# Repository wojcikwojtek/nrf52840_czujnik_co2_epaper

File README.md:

# nrf52840_czujnik_co2_epaper
Projekt czujnika co2, temperatury i wilgotności zrobionym na procesorze nrf52840 z wykorzystaniem wyświetlacza typu epaper komunikującym się poprzez Matter

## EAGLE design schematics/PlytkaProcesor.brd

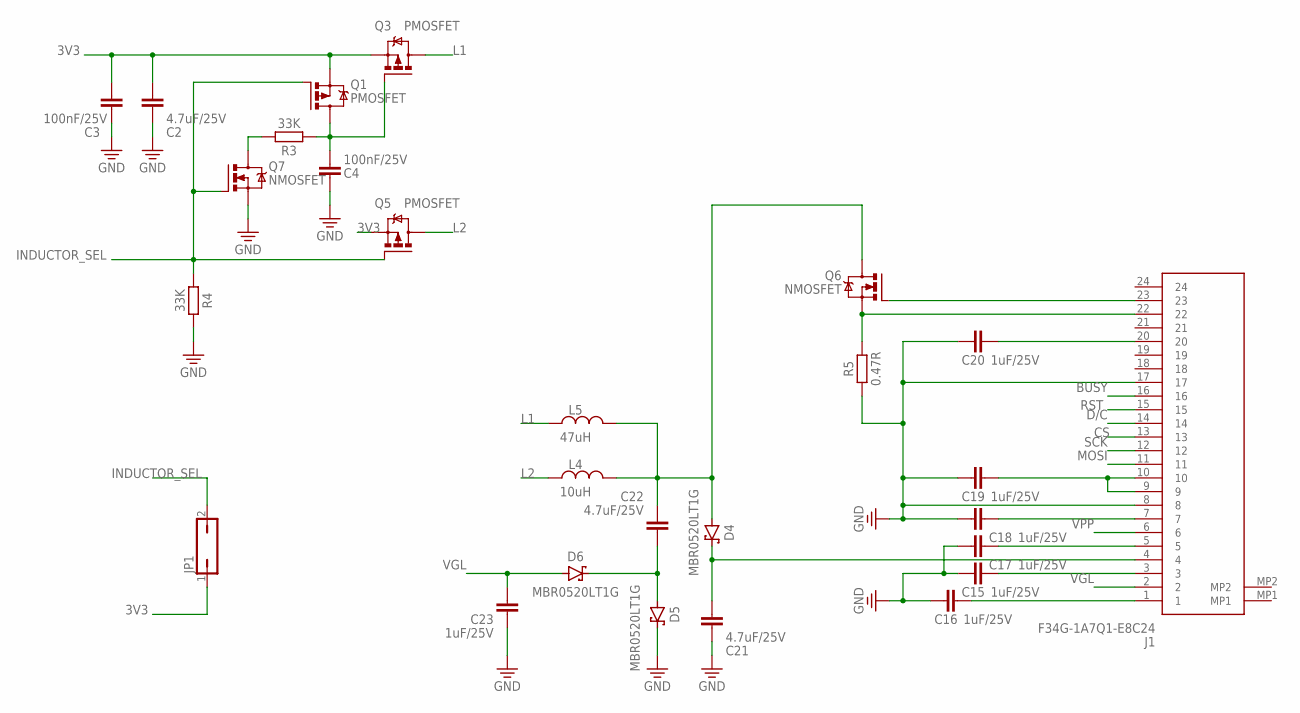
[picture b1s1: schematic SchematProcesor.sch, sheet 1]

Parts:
C2, C21, C22: 4.7uF/25V; CAPC1608X85
C3, C4: 100nF/25V; CAPC1608X85
C15, C16, C17, C18, C19, C20, C23: 1uF/25V; CAPC1608X85
D4, D5, D6: MBR0520LT1G; SODFL3718X115
J1: F34G-1A7Q1-E8C24; F34G1A7Q1E8C24
JP1: JP1Q; JP1
L4: 10uH; INDC1608X95N
L5: 47uH; INDC1608X95N
Q1, Q3, Q5: PMOSFET; SOT23
Q6, Q7: NMOSFET; SOT23
R3, R4: 33K; RESC1608X60
R5: 0.47R; RESC1608X60

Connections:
3V3: C2.2, C3.2, JP1.1, Q1.2 (S), Q3.2 (S), Q5.2 (S); also elsewhere on the board
BUSY: J1.16; also elsewhere on the board
CS: J1.13; also elsewhere on the board
D/C: J1.14; also elsewhere on the board
GND: C2.1, C3.1, C4.1, C15.1, C16.1, C17.1, C18.1, C19.1, C20.1, C21.1, C23.2, D5.1 (C), J1.8, J1.17, Q7.2 (S), R4.2, R5.1; also elsewhere on the board
INDUCTOR_SEL: JP1.2, Q1.1 (G), Q5.1 (G), Q7.1 (G), R4.1
L1: L5.1, Q3.3 (D)
L2: L4.1, Q5.3 (D)
MOSI: J1.11; also elsewhere on the board
unnamed: C4.2, Q1.3 (D), Q3.1 (G), R3.1
unnamed: C16.2, J1.1
unnamed: C15.2, J1.3
unnamed: C17.2, J1.5
unnamed: C18.2, J1.7
unnamed: C19.2, J1.9, J1.10
unnamed: Q7.3 (D), R3.2
unnamed: C20.2, J1.20
unnamed: J1.23, Q6.1 (G)
unnamed: J1.22, Q6.2 (S), R5.2
unnamed: C21.2, D4.1 (C), J1.4
unnamed: C22.1, D4.2 (A), L4.2, L5.2, Q6.3 (D)
unnamed: C22.2, D5.2 (A), D6.1 (C)
RST: J1.15; also elsewhere on the board
SCK: J1.12; also elsewhere on the board
VGL: C23.1, D6.2 (A), J1.2
VPP: J1.6

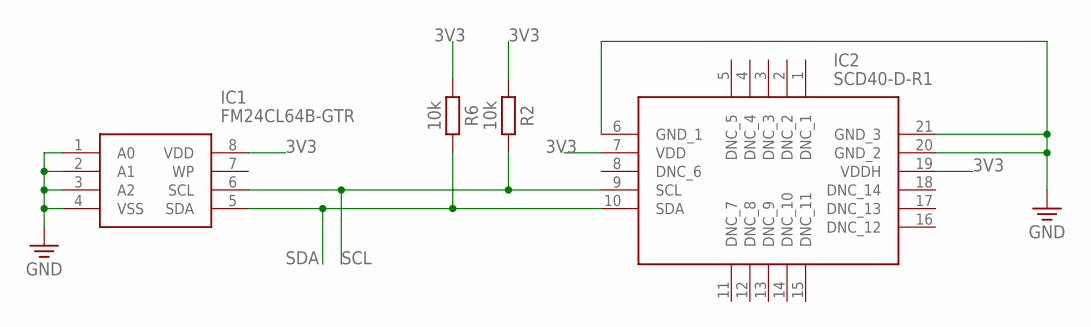
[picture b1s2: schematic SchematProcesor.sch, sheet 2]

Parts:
IC1: FM24CL64B-GTR; SOIC127P602X173-8N
IC2: SCD40-D-R1; SCD40DR1
R2, R6: 10k; RESC1608X60

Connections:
3V3: IC1.8 (VDD), IC2.7 (VDD), IC2.19 (VDDH), R2.1, R6.1; also elsewhere on the board
GND: IC1.1 (A0), IC1.2 (A1), IC1.3 (A2), IC1.4 (VSS), IC2.6 (GND_1), IC2.20 (GND_2), IC2.21 (GND_3); also elsewhere on the board
SCL: IC1.6 (SCL), IC2.9 (SCL), R2.2; also elsewhere on the board
SDA: IC1.5 (SDA), IC2.10 (SDA), R6.2; also elsewhere on the board

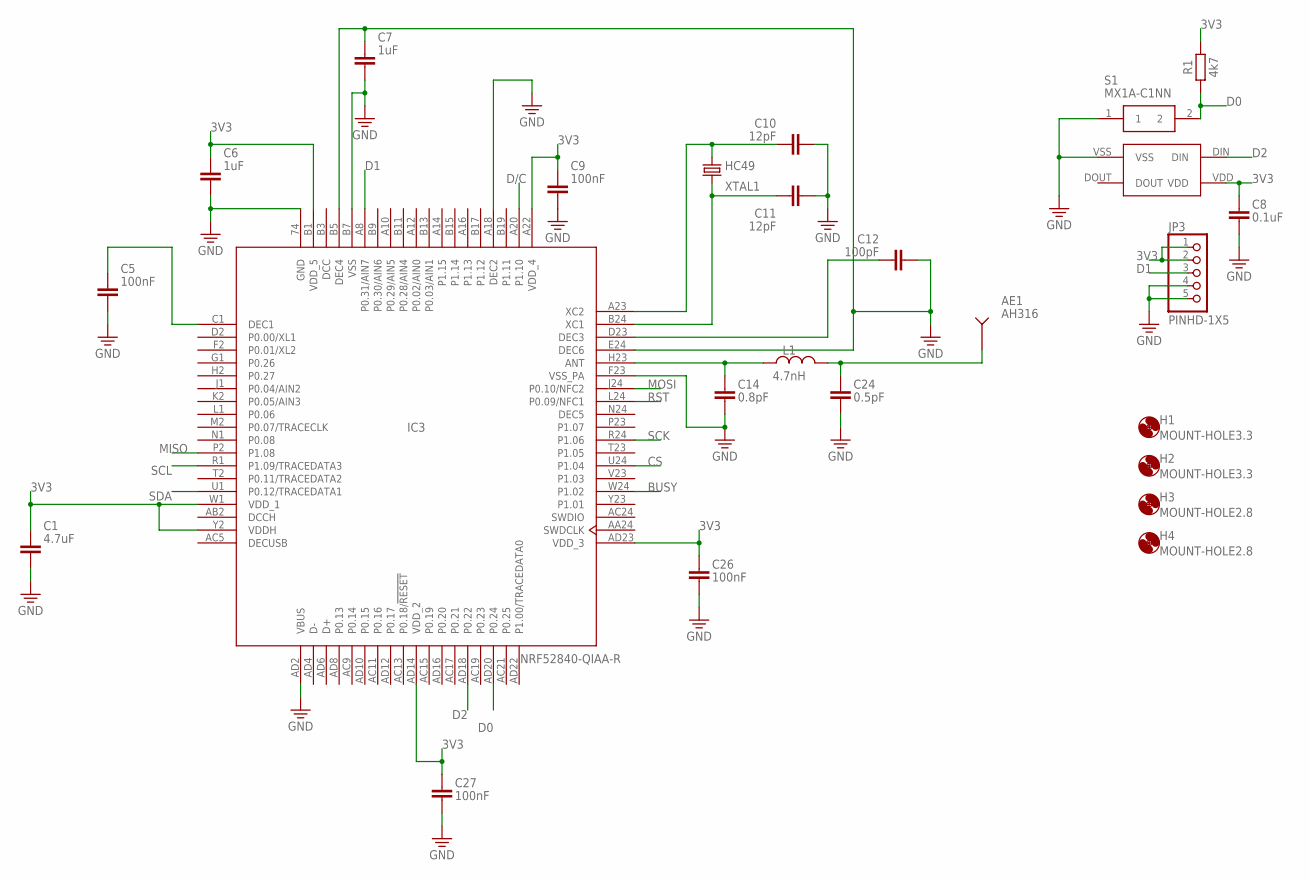
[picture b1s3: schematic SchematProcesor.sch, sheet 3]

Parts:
AE1: AH316; ANT-GPS-3.2X1MM
C1: 4.7uF; CAPC1608X85
C5, C9, C26, C27: 100nF; CAPC1608X85
C6, C7: 1uF; CAPC1608X85
C8: 0.1uF; CAPC1608X85
C10, C11: 12pF; CAPC1608X85
C12: 100pF; CAPC1608X85
C14: 0.8pF; CAPC1608X85
C24: 0.5pF; CAPC1608X85
H1, H2: MOUNT-HOLE3.3; 3,3
H3, H4: MOUNT-HOLE2.8; 2,8
IC3: NRF52840-QIAA-R; NRF52840-QIAA
JP3: PINHD-1X5; 1X05
L1: 4.7nH; INDC1608X95N
R1: 4k7; RESC1005X40
S1: MX1A-C1NN; MX1AC1NN
U$1: N0M59S10IC
XTAL1: HC49; XTALRR488W45L1150T500H350B

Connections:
3V3: C1.1, C6.1, C8.1, C9.1, C26.1, C27.1, IC3.A22 (VDD_4), IC3.AD14 (VDD_2), IC3.AD23 (VDD_3), IC3.B1 (VDD_5), IC3.W1 (VDD_1), IC3.Y2 (VDDH), JP3.1, JP3.2, R1.2, U$1.VDD; also elsewhere on the board
BUSY: IC3.W24 (P1.02); also elsewhere on the board
CS: IC3.U24 (P1.04); also elsewhere on the board
D0: IC3.AD20 (P0.24), R1.1, S1.2
D1: IC3.A8 (P0.31/AIN7), JP3.3
D2: IC3.AD18 (P0.22), U$1.DIN
D/C: IC3.A20 (P1.10); also elsewhere on the board
DCC: IC3.B3 (DCC)
DCCH: IC3.AB2 (DCCH)
DEC5: IC3.N24 (DEC5)
DECUSB: IC3.AC5 (DECUSB)
GND: C1.2, C5.2, C6.2, C7.1, C7.2, C8.2, C9.2, C10.2, C11.2, C12.2, C14.2, C24.2, C26.2, C27.2, IC3.74 (GND), IC3.A18 (DEC2), IC3.AD2 (VBUS), IC3.B5 (DEC4), IC3.B7 (VSS), IC3.E24 (DEC6), IC3.F23 (VSS_PA), JP3.4, JP3.5, S1.1, U$1.VSS; also elsewhere on the board
MISO: IC3.P2 (P1.08)
MOSI: IC3.J24 (P0.10/NFC2); also elsewhere on the board
unnamed: C11.1, IC3.B24 (XC1), XTAL1.2
unnamed: C10.1, IC3.A23 (XC2), XTAL1.1
unnamed: C14.1, IC3.H23 (ANT), L1.1
unnamed: C12.1, IC3.D23 (DEC3)
unnamed: AE1.2 (GND), C24.1, L1.2
unnamed: C5.1, IC3.C1 (DEC1)
RST: IC3.L24 (P0.09/NFC1); also elsewhere on the board
SCK: IC3.R24 (P1.06); also elsewhere on the board
SCL: IC3.R1 (P1.09/TRACEDATA3); also elsewhere on the board
SDA: IC3.U1 (P0.12/TRACEDATA1); also elsewhere on the board

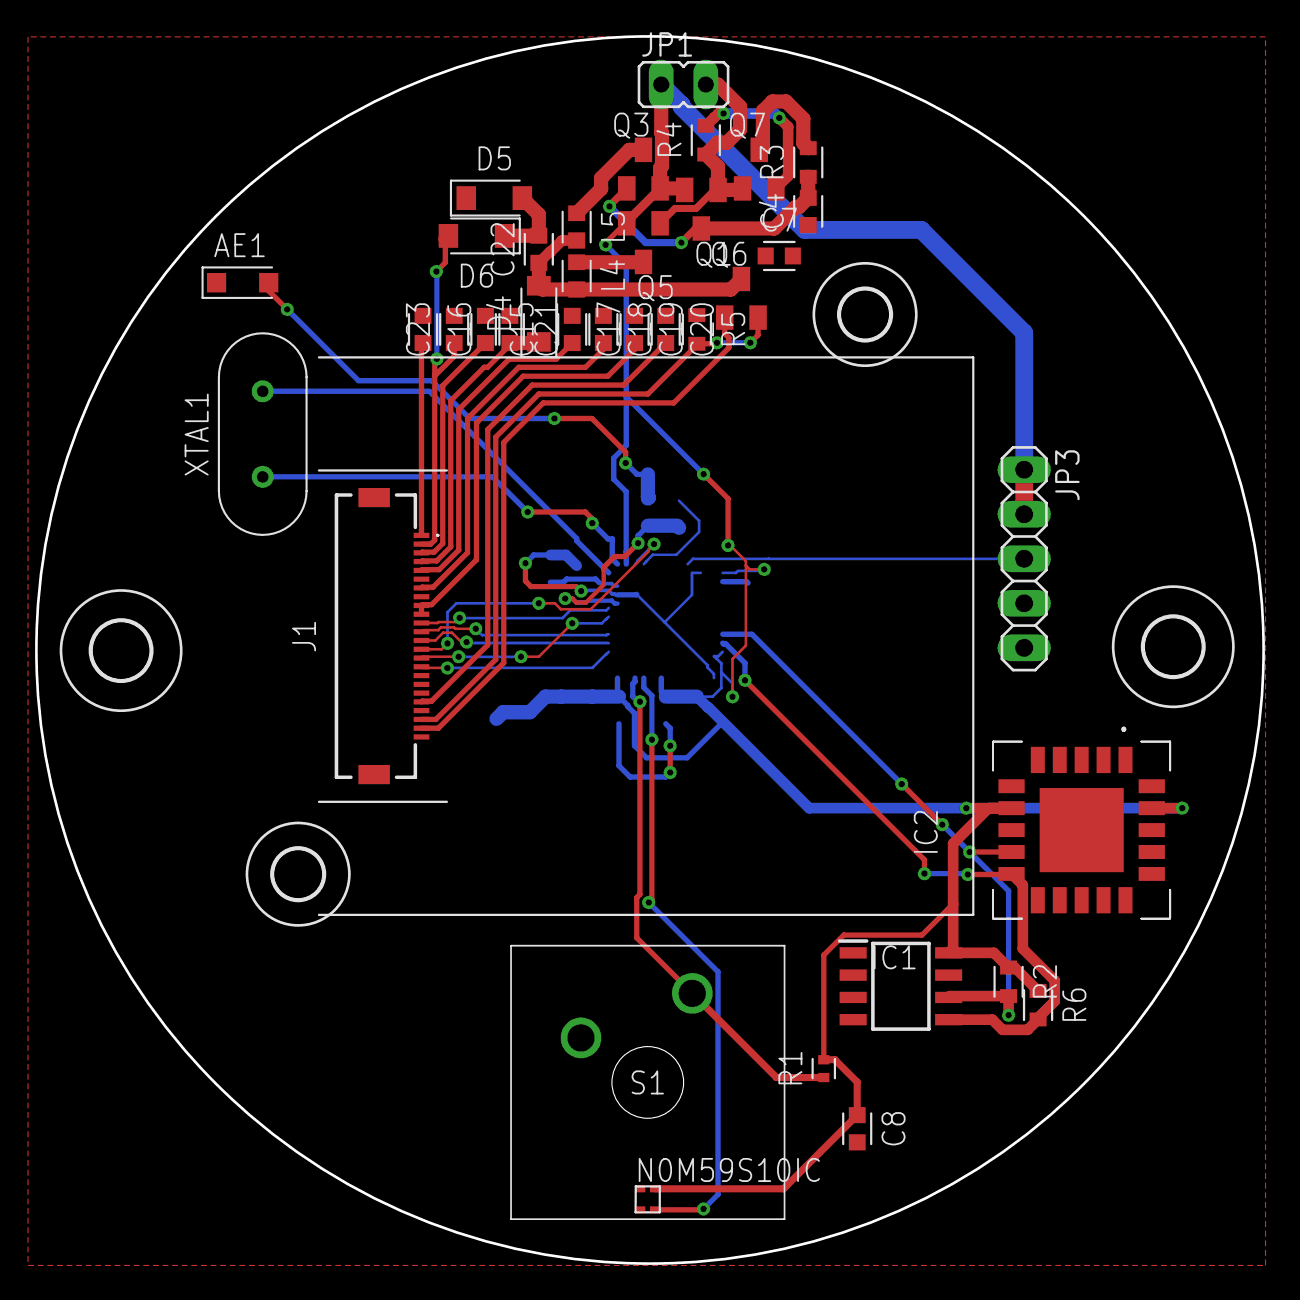
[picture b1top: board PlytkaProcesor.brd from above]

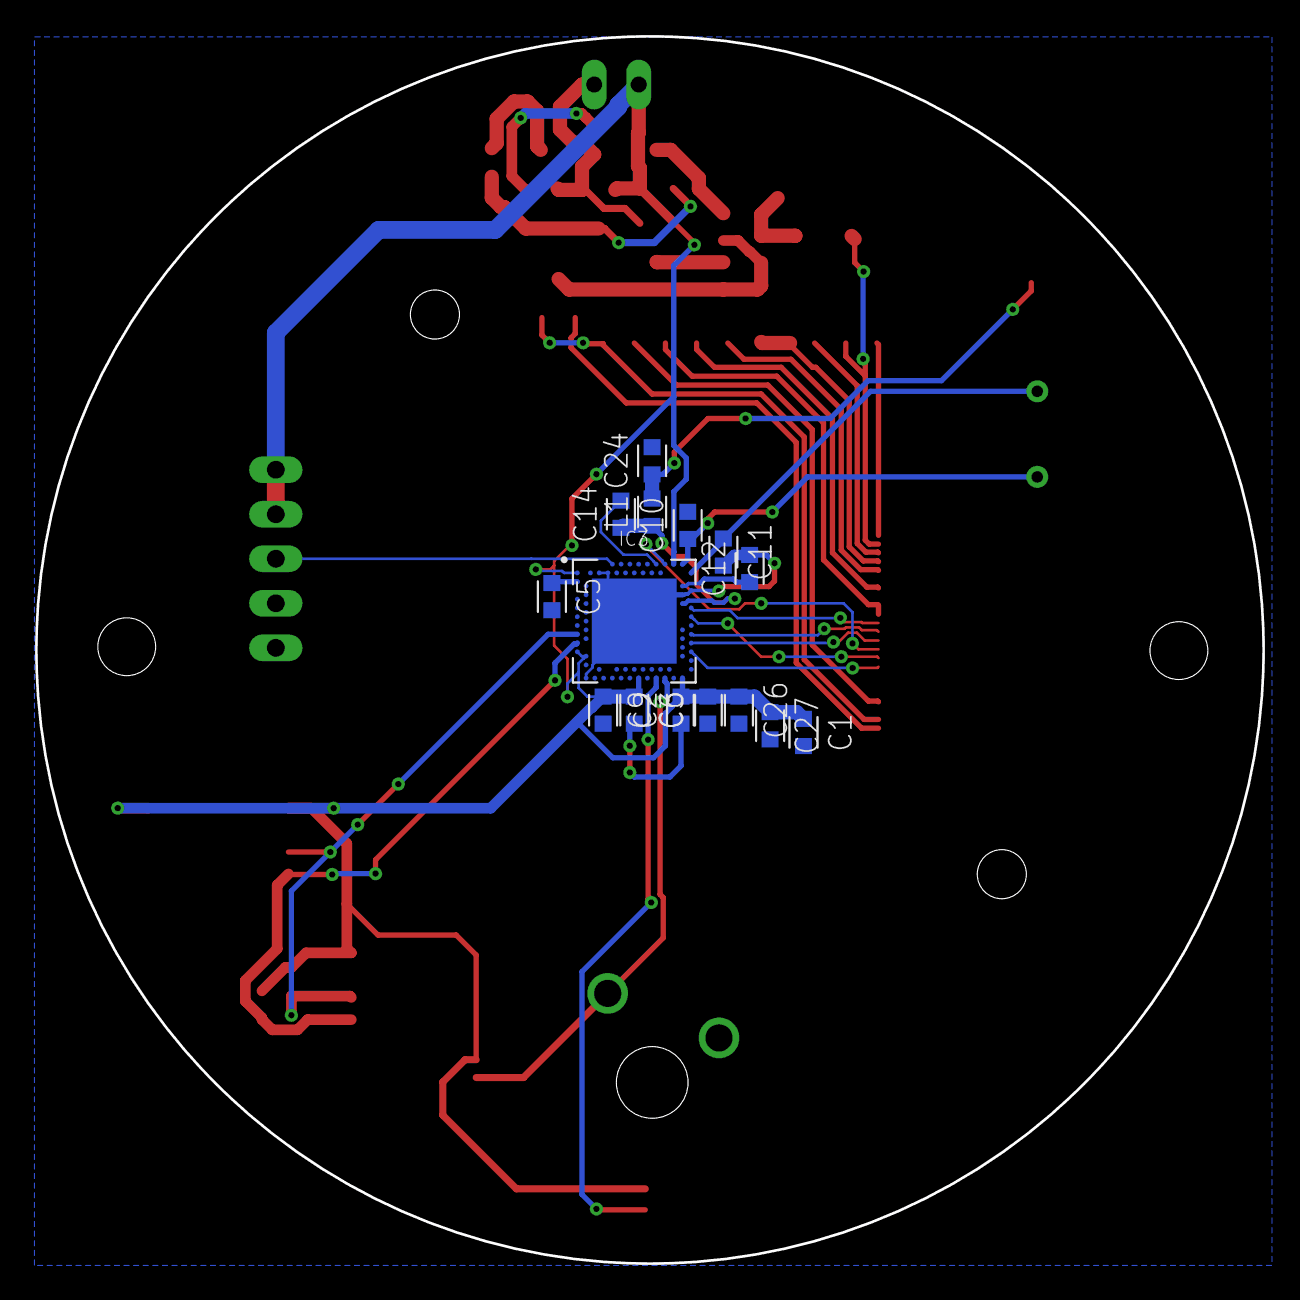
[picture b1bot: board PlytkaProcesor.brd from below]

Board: 2 copper layers, 70.0 x 70.0 mm, 56 parts (15 on the bottom side), 36 nets.

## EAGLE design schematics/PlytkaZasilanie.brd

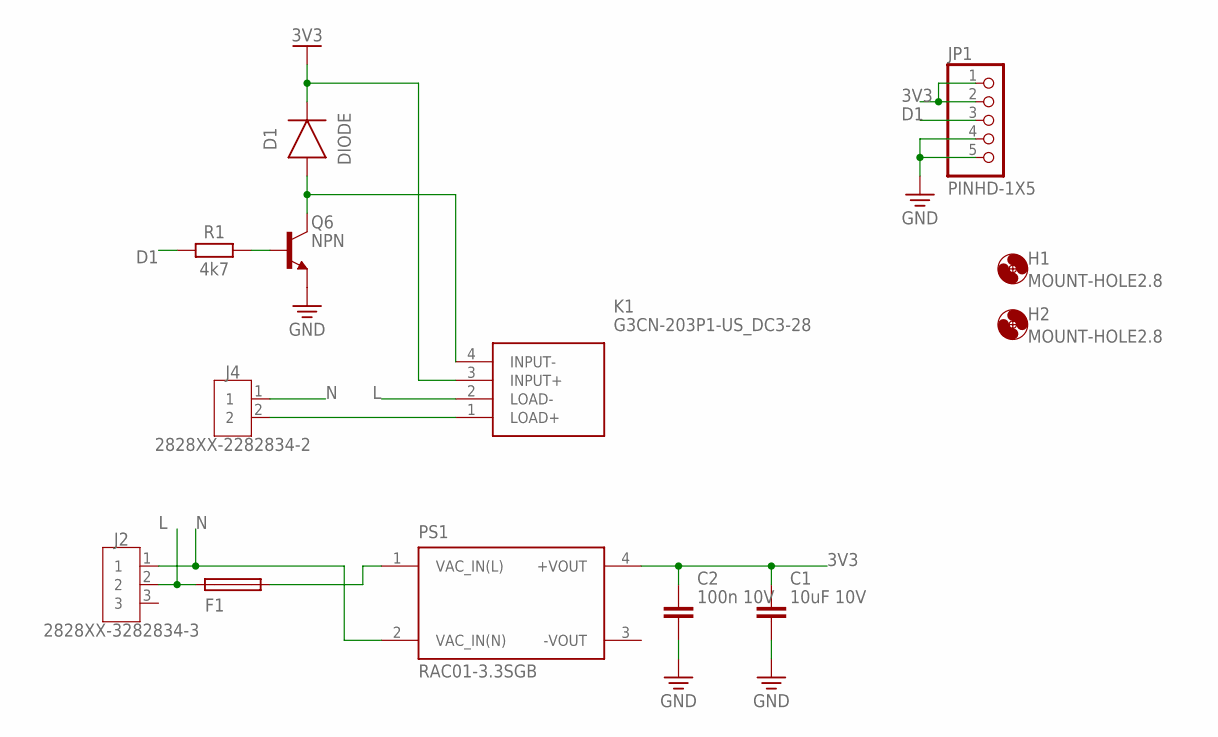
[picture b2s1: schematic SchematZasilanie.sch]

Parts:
C1: 10uF 10V; CAPC3216X135
C2: 100n 10V; CAPC3216X135
D1: DIODE; DIOMELF3516
F1: FUSE_CHIP-1206(3216-METRIC); FUSC3215X82N
H1, H2: MOUNT-HOLE2.8; 2,8
J2: 2828XX-3282834-3; TERMBLK_254-3N
J4: 2828XX-2282834-2; TERMBLK_254-2N
JP1: PINHD-1X5; 1X05
K1: G3CN-203P1-US_DC3-28; G3CN203P1USDC328
PS1: RAC01-3.3SGB; CONV_RAC01-3.3SGB
Q6: NPN; TO18
R1: 4k7; RESC1608X60

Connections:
3V3: C1.1, C2.1, D1.1 (C), JP1.1, JP1.2, K1.3 (INPUT+), PS1.4 (+VOUT)
D1: JP1.3, R1.1
GND: C1.2, C2.2, JP1.4, JP1.5, Q6.1 (E)
L: F1.1, J2.2, K1.2 (LOAD-)
N: J2.1, J4.1, PS1.2 (VAC_IN(N))
unnamed: J4.2, K1.1 (LOAD+)
unnamed: F1.2, PS1.1 (VAC_IN(L))
unnamed: Q6.2 (B), R1.2
unnamed: D1.2 (A), K1.4 (INPUT-), Q6.3 (C)

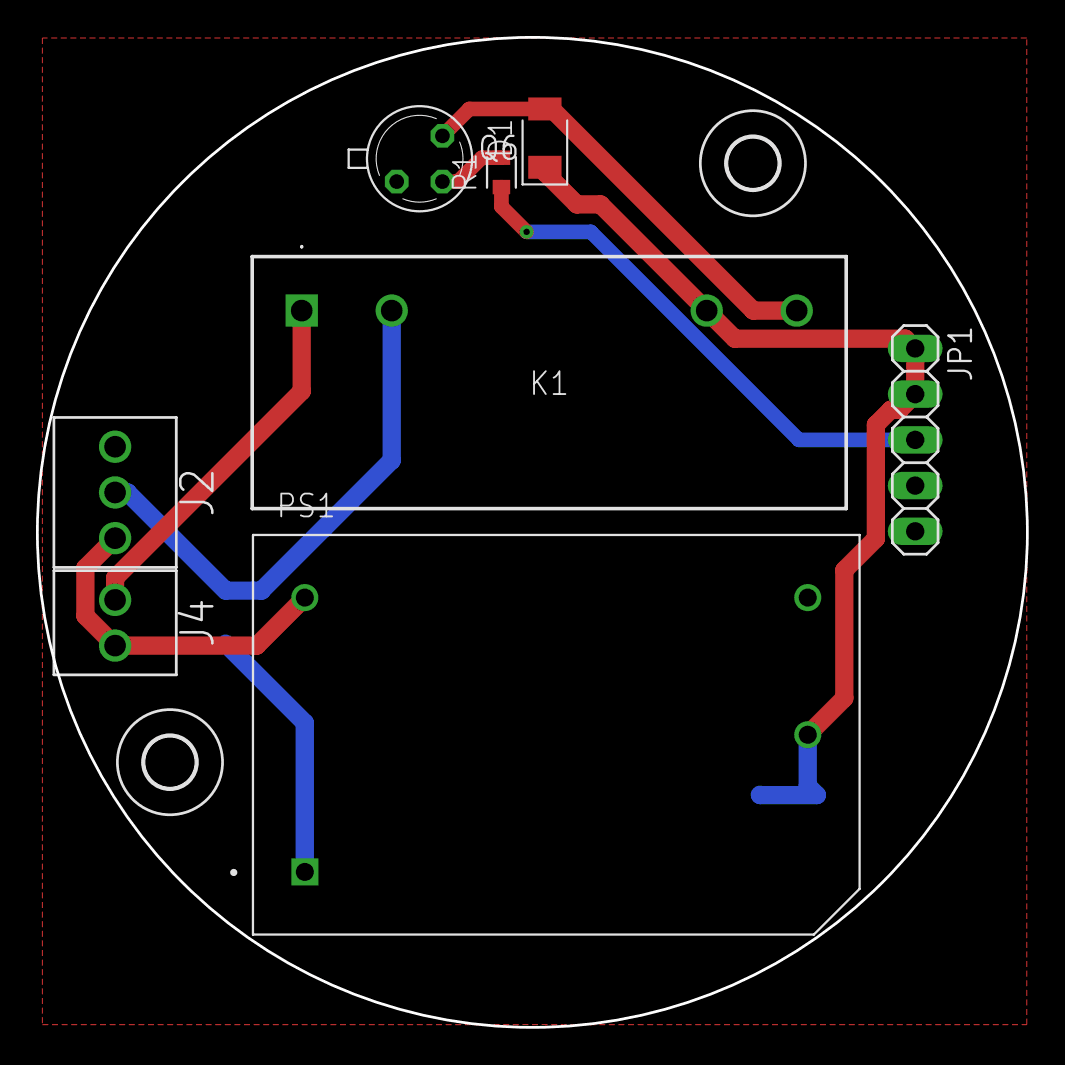
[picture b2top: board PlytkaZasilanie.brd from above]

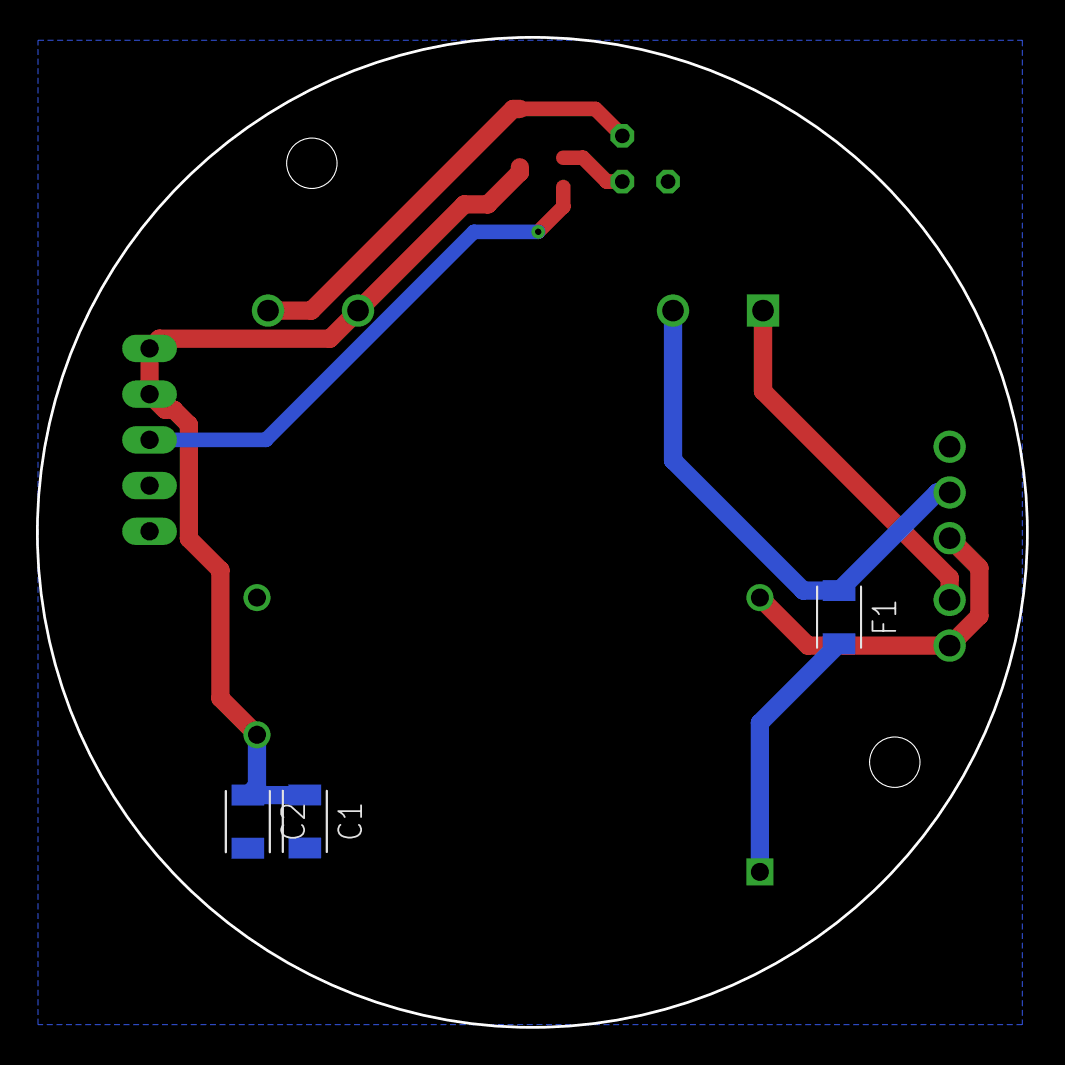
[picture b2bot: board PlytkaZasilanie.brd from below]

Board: 2 copper layers, 55.0 x 55.0 mm, 13 parts (3 on the bottom side), 9 nets.

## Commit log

2023-12-02 Add files via upload
    Próbowałem pozmieniać bibliotekę dla wyświetlacza tak by współpracowała z Zephyrem. Doszedłem do etapu gdzie sama biblioteka się kompiluje ale jak chcemy stworzyć obiekt klasy Screen_EPD_EXT3 to nagl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
2023-12-24 Naprawiłem problem ze stringami zastępując je char*
2023-12-29 Biblioteka już działa i wyświetla pomiary czujnika na ekranie
2024-01-10 Wrzuciłem program napisany pod matter template
2024-02-01 Załadowano najnowszą wersję
2024-02-13 Project Final
